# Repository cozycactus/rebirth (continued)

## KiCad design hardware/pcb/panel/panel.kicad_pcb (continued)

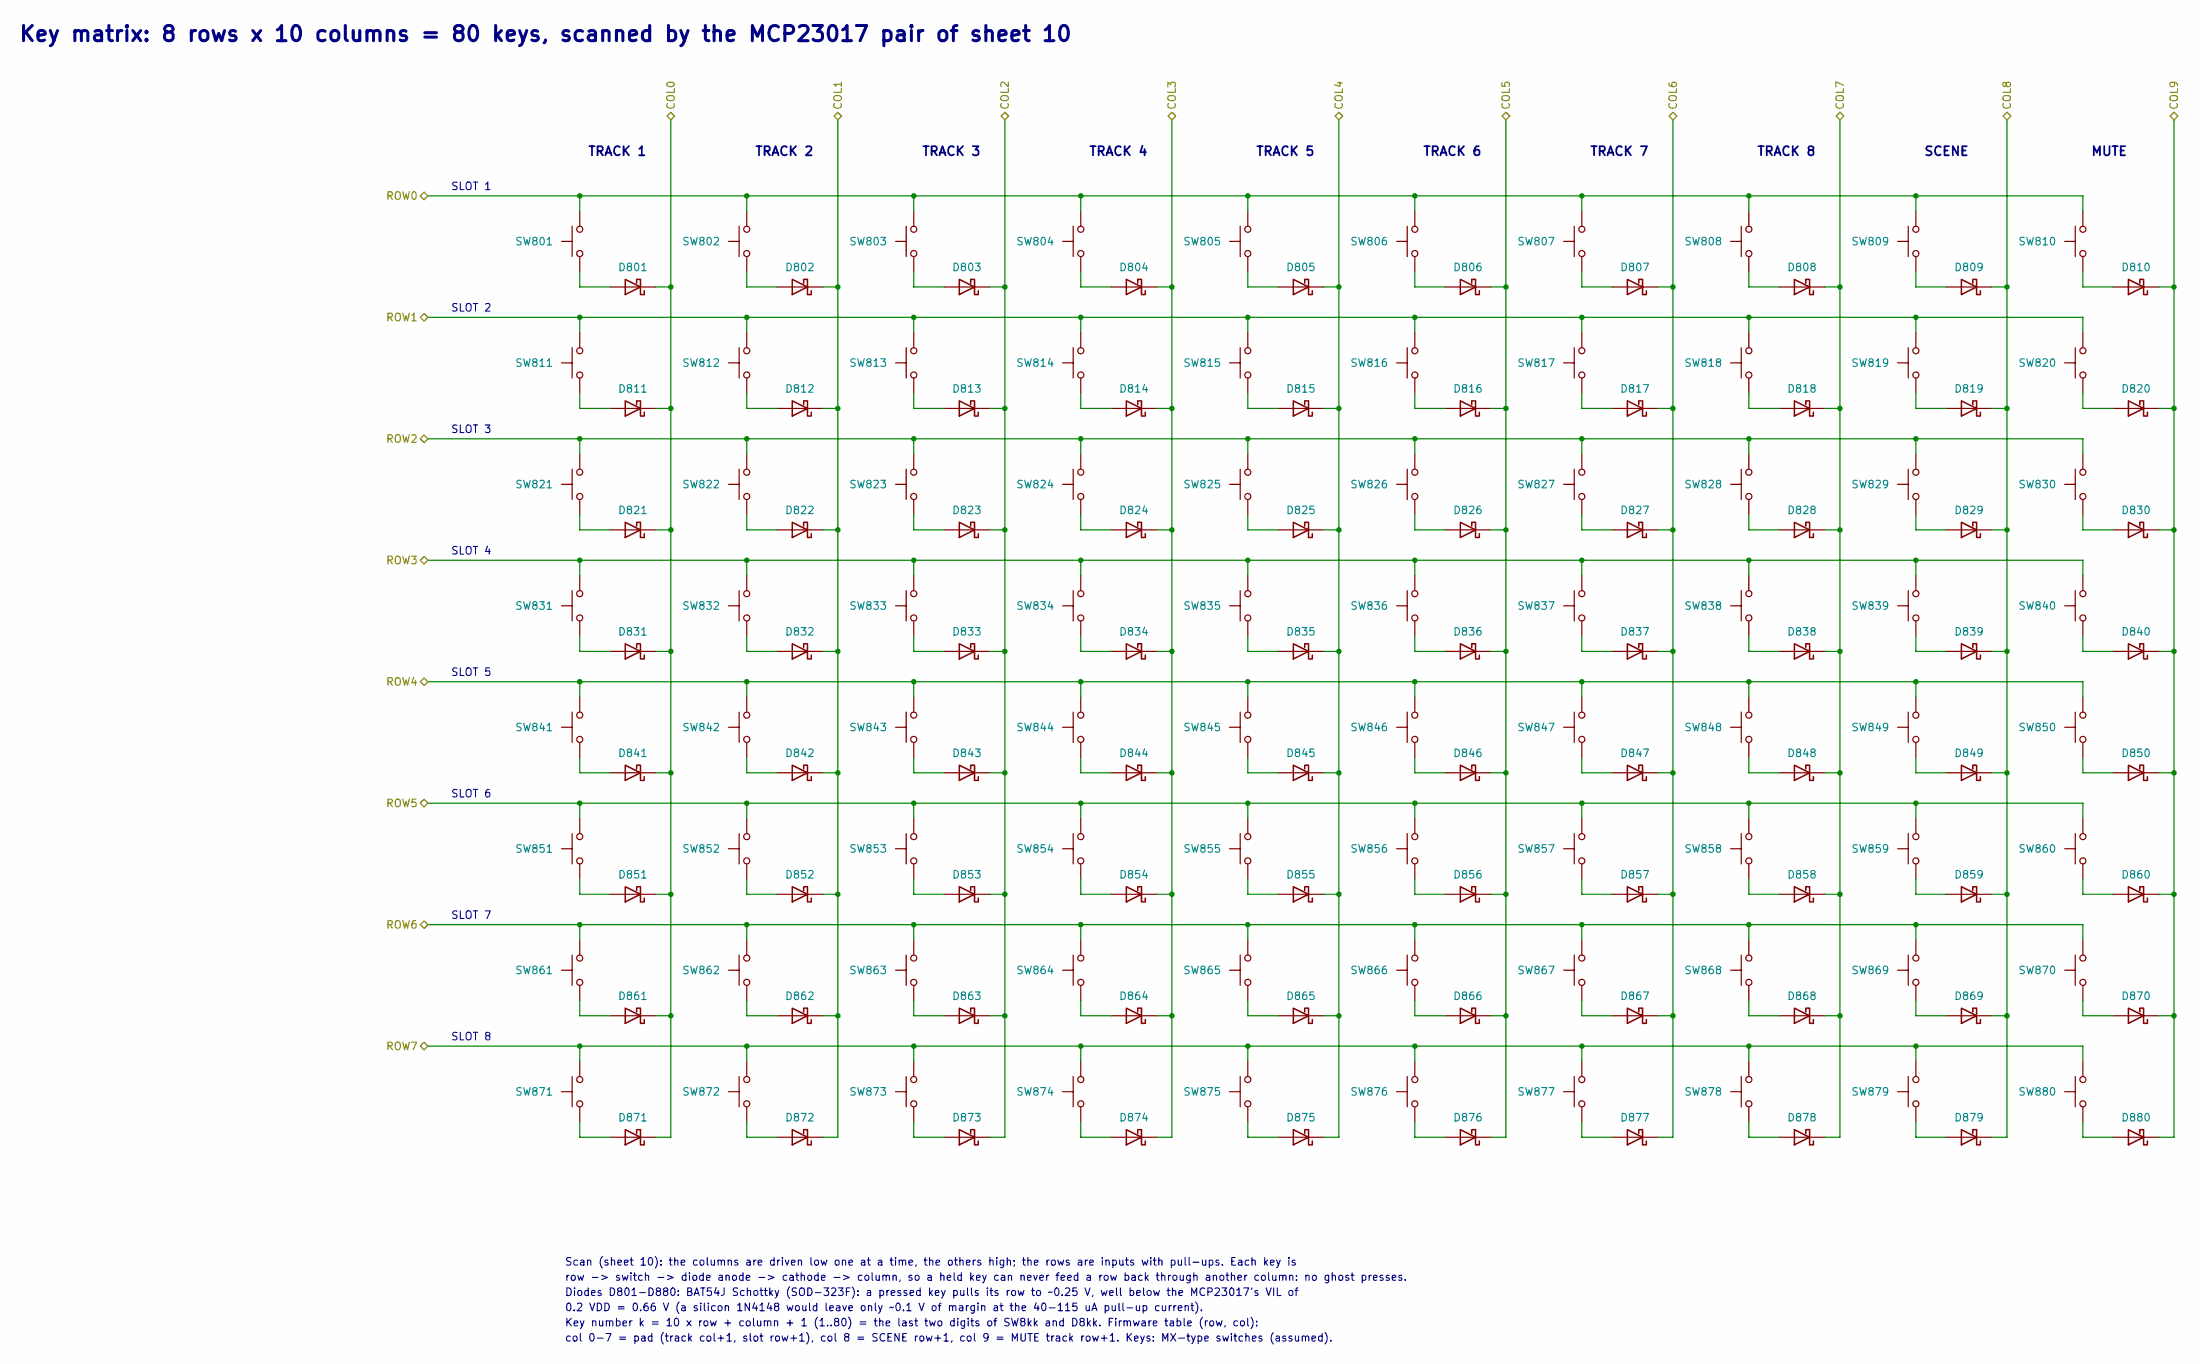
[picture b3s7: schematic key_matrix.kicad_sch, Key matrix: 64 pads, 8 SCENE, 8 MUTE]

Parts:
D801, D802, D803, D804, D805, D806, D807, D808, D809, D810, D811, D812, D813, D814, D815, D816, D817, D818, D819, D820, D821, D822, D823, D824, D825, D826, D827, D828, D829, D830, D831, D832, D833, D834, D835, D836, D837, D838, D839, D840, D841, D842, D843, D844, D845, D846, D847, D848, D849, D850, D851, D852, D853, D854, D855, D856, D857, D858, D859, D860, D861, D862, D863, D864, D865, D866, D867, D868, D869, D870, D871, D872, D873, D874, D875, D876, D877, D878, D879, D880: BAT54J; D_SOD-323F
SW801, SW802, SW803, SW804, SW805, SW806, SW807, SW808, SW809, SW810, SW811, SW812, SW813, SW814, SW815, SW816, SW817, SW818, SW819, SW820, SW821, SW822, SW823, SW824, SW825, SW826, SW827, SW828, SW829, SW830, SW831, SW832, SW833, SW834, SW835, SW836, SW837, SW838, SW839, SW840, SW841, SW842, SW843, SW844, SW845, SW846, SW847, SW848, SW849, SW850, SW851, SW852, SW853, SW854, SW855, SW856, SW857, SW858, SW859, SW860, SW861, SW862, SW863, SW864, SW865, SW866, SW867, SW868, SW869, SW870, SW871, SW872, SW873, SW874, SW875, SW876, SW877, SW878, SW879, SW880: MX; SW_Cherry_MX_1.00u_PCB

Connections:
/COL0: D801.1 (K), D811.1 (K), D821.1 (K), D831.1 (K), D841.1 (K), D851.1 (K), D861.1 (K), D871.1 (K); also elsewhere on the board
/COL1: D802.1 (K), D812.1 (K), D822.1 (K), D832.1 (K), D842.1 (K), D852.1 (K), D862.1 (K), D872.1 (K); also elsewhere on the board
/COL2: D803.1 (K), D813.1 (K), D823.1 (K), D833.1 (K), D843.1 (K), D853.1 (K), D863.1 (K), D873.1 (K); also elsewhere on the board
/COL3: D804.1 (K), D814.1 (K), D824.1 (K), D834.1 (K), D844.1 (K), D854.1 (K), D864.1 (K), D874.1 (K); also elsewhere on the board
/COL4: D805.1 (K), D815.1 (K), D825.1 (K), D835.1 (K), D845.1 (K), D855.1 (K), D865.1 (K), D875.1 (K); also elsewhere on the board
/COL5: D806.1 (K), D816.1 (K), D826.1 (K), D836.1 (K), D846.1 (K), D856.1 (K), D866.1 (K), D876.1 (K); also elsewhere on the board
/COL6: D807.1 (K), D817.1 (K), D827.1 (K), D837.1 (K), D847.1 (K), D857.1 (K), D867.1 (K), D877.1 (K); also elsewhere on the board
/COL7: D808.1 (K), D818.1 (K), D828.1 (K), D838.1 (K), D848.1 (K), D858.1 (K), D868.1 (K), D878.1 (K); also elsewhere on the board
/COL8: D809.1 (K), D819.1 (K), D829.1 (K), D839.1 (K), D849.1 (K), D859.1 (K), D869.1 (K), D879.1 (K); also elsewhere on the board
/COL9: D810.1 (K), D820.1 (K), D830.1 (K), D840.1 (K), D850.1 (K), D860.1 (K), D870.1 (K), D880.1 (K); also elsewhere on the board
/ROW0: SW801.2, SW802.2, SW803.2, SW804.2, SW805.2, SW806.2, SW807.2, SW808.2, SW809.2, SW810.2; also elsewhere on the board
/ROW1: SW811.2, SW812.2, SW813.2, SW814.2, SW815.2, SW816.2, SW817.2, SW818.2, SW819.2, SW820.2; also elsewhere on the board
/ROW2: SW821.2, SW822.2, SW823.2, SW824.2, SW825.2, SW826.2, SW827.2, SW828.2, SW829.2, SW830.2; also elsewhere on the board
/ROW3: SW831.2, SW832.2, SW833.2, SW834.2, SW835.2, SW836.2, SW837.2, SW838.2, SW839.2, SW840.2; also elsewhere on the board
/ROW4: SW841.2, SW842.2, SW843.2, SW844.2, SW845.2, SW846.2, SW847.2, SW848.2, SW849.2, SW850.2; also elsewhere on the board
/ROW5: SW851.2, SW852.2, SW853.2, SW854.2, SW855.2, SW856.2, SW857.2, SW858.2, SW859.2, SW860.2; also elsewhere on the board
/ROW6: SW861.2, SW862.2, SW863.2, SW864.2, SW865.2, SW866.2, SW867.2, SW868.2, SW869.2, SW870.2; also elsewhere on the board
/ROW7: SW871.2, SW872.2, SW873.2, SW874.2, SW875.2, SW876.2, SW877.2, SW878.2, SW879.2, SW880.2; also elsewhere on the board
unnamed: D801.2 (A), SW801.1
unnamed: D802.2 (A), SW802.1
unnamed: D803.2 (A), SW803.1
unnamed: D804.2 (A), SW804.1
unnamed: D805.2 (A), SW805.1
unnamed: D806.2 (A), SW806.1
unnamed: D807.2 (A), SW807.1
unnamed: D808.2 (A), SW808.1
unnamed: D809.2 (A), SW809.1
unnamed: D810.2 (A), SW810.1
unnamed: D811.2 (A), SW811.1
unnamed: D812.2 (A), SW812.1
unnamed: D813.2 (A), SW813.1
unnamed: D814.2 (A), SW814.1
unnamed: D815.2 (A), SW815.1
unnamed: D816.2 (A), SW816.1
unnamed: D817.2 (A), SW817.1
unnamed: D818.2 (A), SW818.1
unnamed: D819.2 (A), SW819.1
unnamed: D820.2 (A), SW820.1
unnamed: D821.2 (A), SW821.1
unnamed: D822.2 (A), SW822.1
unnamed: D823.2 (A), SW823.1
unnamed: D824.2 (A), SW824.1
unnamed: D825.2 (A), SW825.1
unnamed: D826.2 (A), SW826.1
unnamed: D827.2 (A), SW827.1
unnamed: D828.2 (A), SW828.1
unnamed: D829.2 (A), SW829.1
unnamed: D830.2 (A), SW830.1
unnamed: D831.2 (A), SW831.1
unnamed: D832.2 (A), SW832.1
unnamed: D833.2 (A), SW833.1
unnamed: D834.2 (A), SW834.1
unnamed: D835.2 (A), SW835.1
unnamed: D836.2 (A), SW836.1
unnamed: D837.2 (A), SW837.1
unnamed: D838.2 (A), SW838.1
unnamed: D839.2 (A), SW839.1
unnamed: D840.2 (A), SW840.1
unnamed: D841.2 (A), SW841.1
unnamed: D842.2 (A), SW842.1
unnamed: D843.2 (A), SW843.1
unnamed: D844.2 (A), SW844.1
unnamed: D845.2 (A), SW845.1
unnamed: D846.2 (A), SW846.1
unnamed: D847.2 (A), SW847.1
unnamed: D848.2 (A), SW848.1
unnamed: D849.2 (A), SW849.1
unnamed: D850.2 (A), SW850.1
unnamed: D851.2 (A), SW851.1
unnamed: D852.2 (A), SW852.1
unnamed: D853.2 (A), SW853.1
unnamed: D854.2 (A), SW854.1
unnamed: D855.2 (A), SW855.1
unnamed: D856.2 (A), SW856.1
unnamed: D857.2 (A), SW857.1
unnamed: D858.2 (A), SW858.1
unnamed: D859.2 (A), SW859.1
unnamed: D860.2 (A), SW860.1
unnamed: D861.2 (A), SW861.1
unnamed: D862.2 (A), SW862.1
unnamed: D863.2 (A), SW863.1
unnamed: D864.2 (A), SW864.1
unnamed: D865.2 (A), SW865.1
unnamed: D866.2 (A), SW866.1
unnamed: D867.2 (A), SW867.1
unnamed: D868.2 (A), SW868.1
unnamed: D869.2 (A), SW869.1
unnamed: D870.2 (A), SW870.1
unnamed: D871.2 (A), SW871.1
unnamed: D872.2 (A), SW872.1
unnamed: D873.2 (A), SW873.1
unnamed: D874.2 (A), SW874.1
unnamed: D875.2 (A), SW875.1
unnamed: D876.2 (A), SW876.1
unnamed: D877.2 (A), SW877.1
unnamed: D878.2 (A), SW878.1
unnamed: D879.2 (A), SW879.1
unnamed: D880.2 (A), SW880.1

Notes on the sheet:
Key matrix: 8 rows x 10 columns = 80 keys, scanned by the MCP23017 pair of sheet 10
SLOT 1
SLOT 2
SLOT 3
SLOT 4
SLOT 5
SLOT 6
SLOT 7
SLOT 8
TRACK 1
TRACK 2
TRACK 3
TRACK 4
TRACK 5
TRACK 6
TRACK 7
TRACK 8
SCENE
MUTE
Scan (sheet 10): the columns are driven low one at a time, the others high; the rows are inputs with pull-ups. Each key is
row -> switch -> diode anode -> cathode -> column, so a held key can never feed a row back through another column: no ghost presses.
Diodes D801-D880: BAT54J Schottky (SOD-323F): a pressed key pulls its row to ~0.25 V, well below the MCP23017's VIL of
0.2 VDD = 0.66 V (a silicon 1N4148 would leave only ~0.1 V of margin at the 40-115 uA pull-up current).
Key number k = 10 x row + column + 1 (1..80) = the last two digits of SW8kk and D8kk. Firmware table (row, col):
col 0-7 = pad (track col+1, slot row+1), col 8 = SCENE row+1, col 9 = MUTE track row+1. Keys: MX-type switches (assumed).

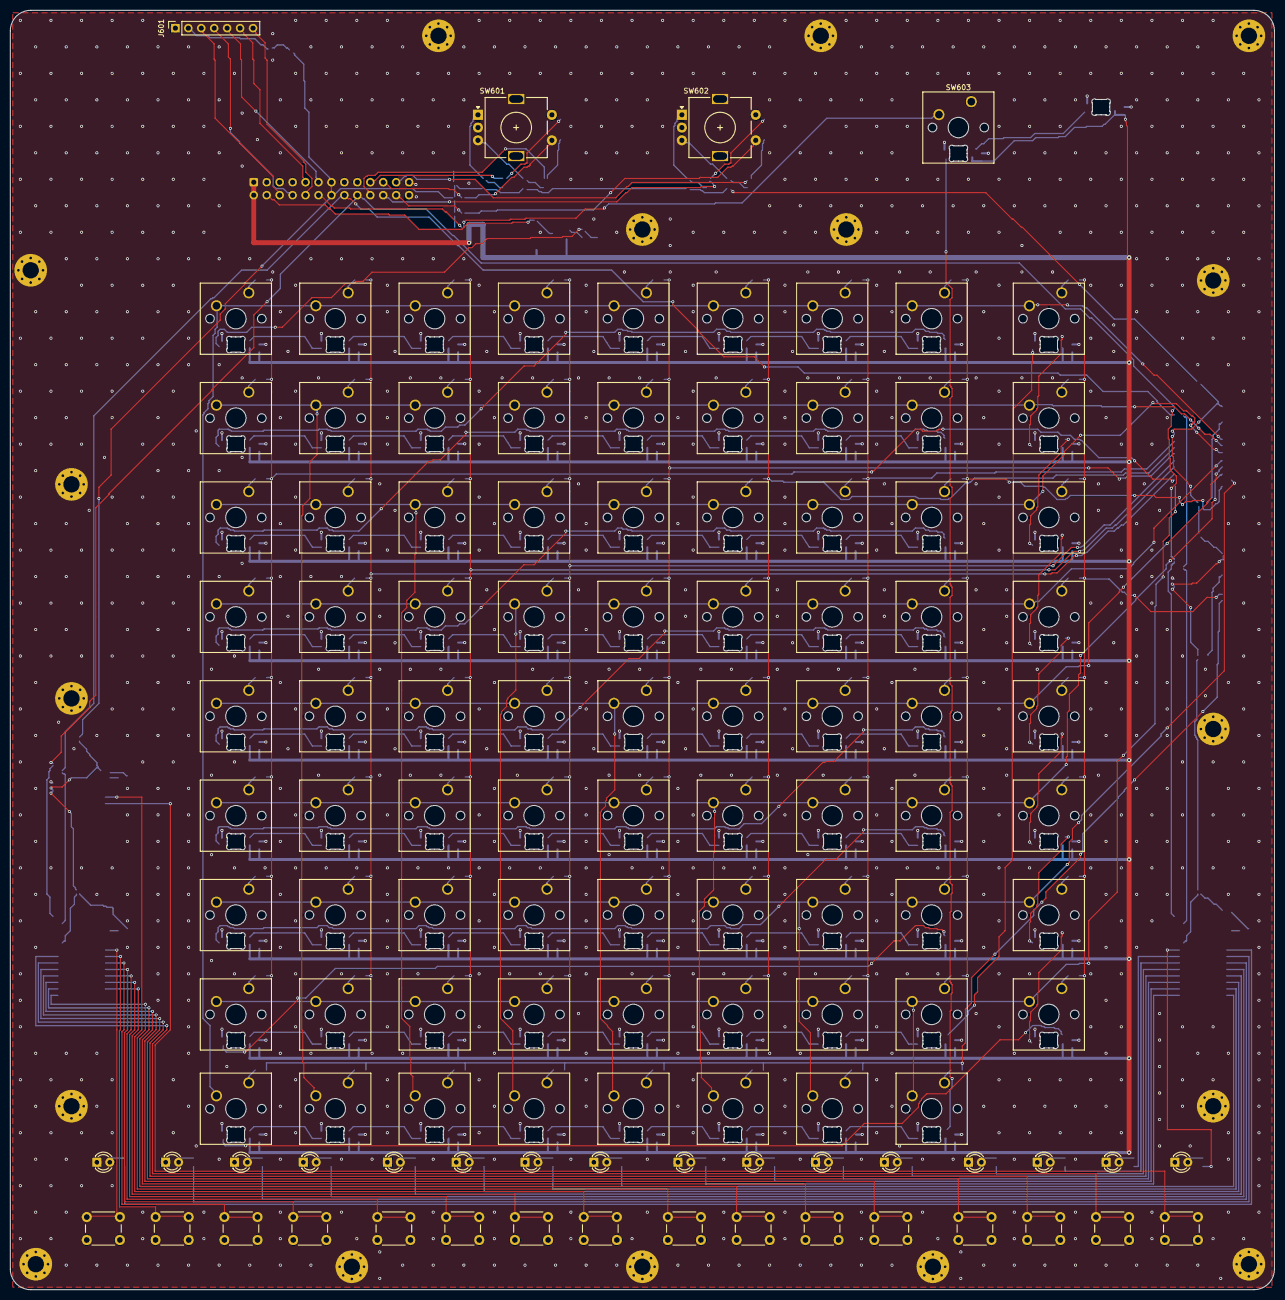
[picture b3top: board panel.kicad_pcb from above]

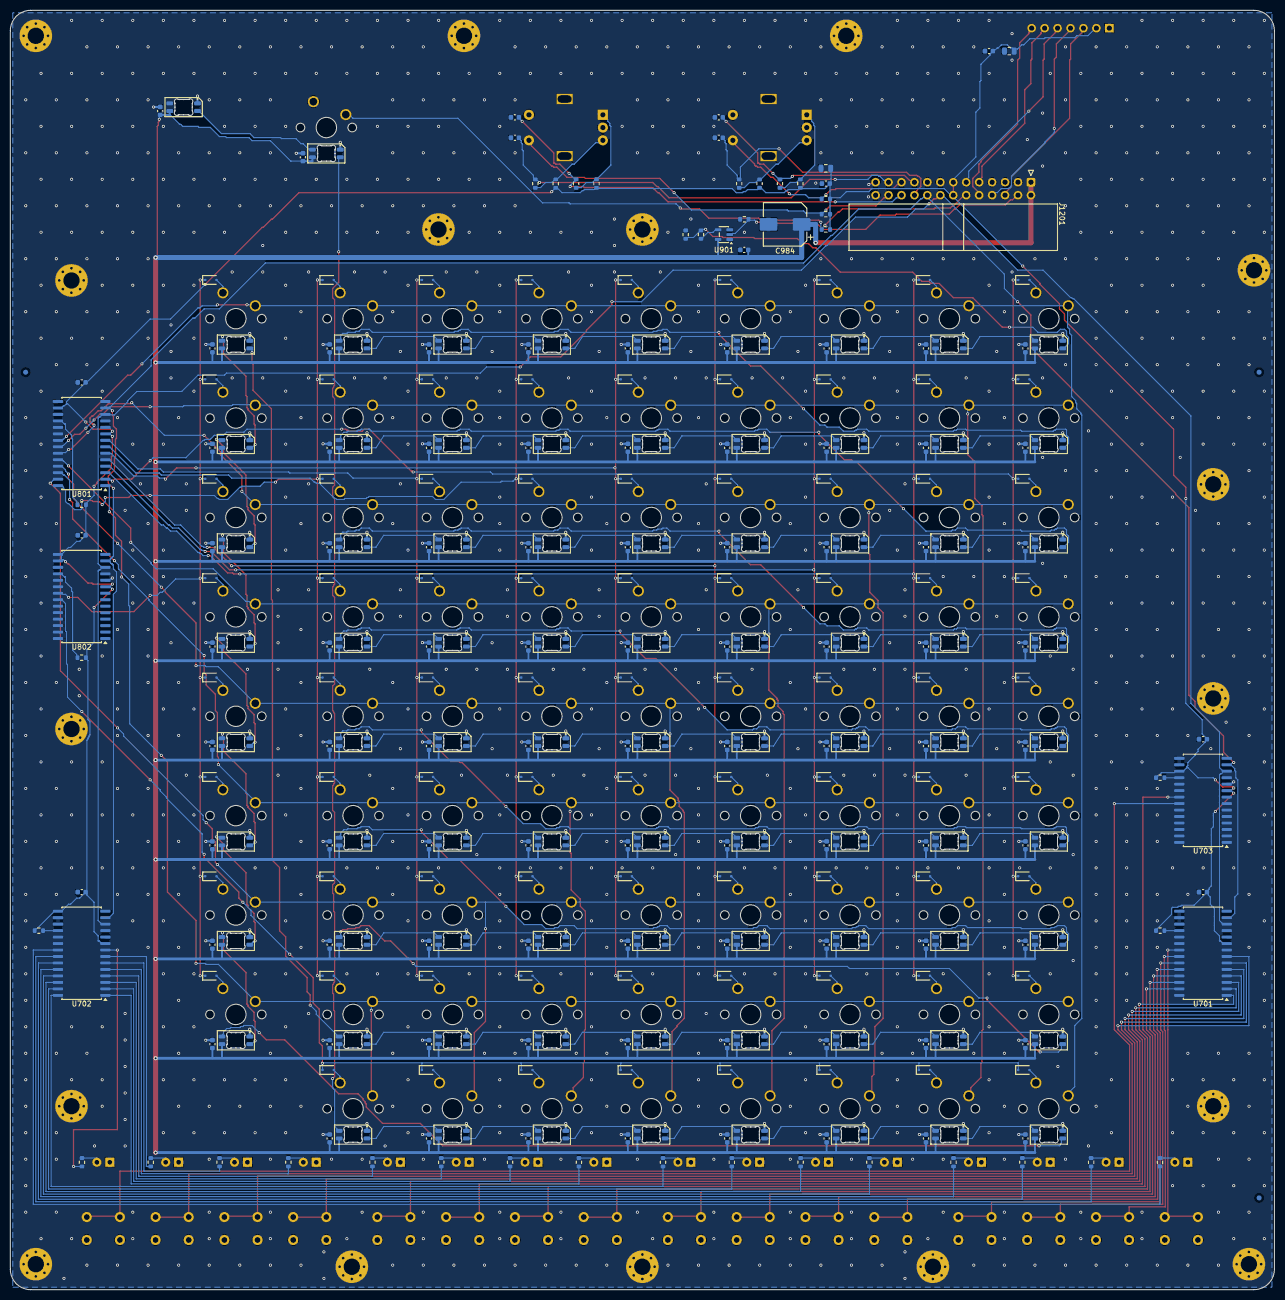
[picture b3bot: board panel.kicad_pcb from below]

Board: 2 copper layers, 248.0 x 251.0 mm, 437 parts (304 on the bottom side), 256 nets.

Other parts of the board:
FID1, FID2, FID3: Fiducial_1mm_Mask2mm
H1, H2, H3, H4, H5, H6, H7, H8, H9, H10, H11, H12, H13, H14, H15, H16, H17: MountingHole_3.2mm_M3_Pad_Via

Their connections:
GND: H1.1, H2.1, H3.1, H4.1, H5.1, H6.1, H7.1, H8.1, H9.1, H10.1, H11.1, H12.1, H13.1, H14.1, H15.1, H16.1, H17.1; also elsewhere on the board

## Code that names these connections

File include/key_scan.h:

#ifndef KEY_SCAN_H
#define KEY_SCAN_H

#include <stdbool.h>
#include <stdint.h>

// The 8 x 10 key matrix on two MCP23017 (I2C0, BANK = 0). Each key is
// row -> switch -> diode -> column: rows are inputs with pull-ups, columns
// push-pull outputs, the selected one low.
#define KEY_SCAN_ROW_ADDR 0x22   // U801: GPA0-6 = ROW0-6, GPB0 = ROW7, GPB1-7 = COL0-6, GPA7 = COL7
#define KEY_SCAN_COL_ADDR 0x23   // U802: GPA0 = COL8, GPA1 = COL9, other pins open
#define KEY_SCAN_ROWS 8
#define KEY_SCAN_COLS 10

// Configures both chips, IODIR (the canary) first on each: U801 IODIR 7F/01,
// IPOL 00/00, GPPU 7F/01, OLAT FF/FF, then U802 IODIR 00/00, OLAT FF/FF.
// Does not bring the bus up (mcp23017_init does). The column selection is
// unknown afterwards, whatever the result.
bool key_scan_init(void);

// Reads U801 IODIR and IPOL and U802 IODIR back. False on an I2C error;
// otherwise *intact tells whether all six bytes hold what key_scan_init
// wrote. A chip that reset after its canary was written reads not intact.
bool key_scan_check(bool *intact);

// Selects column col (0-9) and reads the rows: *down bit r = ROW r low. A
// column that may still be low is released first, so at most one column is
// low when the rows are read. False on an I2C error: *down is not written
// and the selection becomes unknown, so the next step releases both chips'
// columns as needed. A col of KEY_SCAN_COLS or more is refused: false, with
// no transfer and the selection unchanged.
bool key_scan_column(uint8_t col, uint8_t *down);

// Reads back only the canaries a reset clears, after the sample of column col
// (0-9): U801 IODIR for COL0-7 (pointer write and 2 bytes), and U802 IODIR as
// well for COL8/9. False on an I2C error, or with no transfer for a col of
// KEY_SCAN_COLS or more; *intact is then not written. Otherwise *intact tells
// whether those bytes hold what key_scan_init wrote. IPOL is left to
// key_scan_check. The column selection is not touched.
bool key_scan_verify(uint8_t col, bool *intact);

#endif

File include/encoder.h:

#ifndef ENCODER_H
#define ENCODER_H

#include <stdint.h>
#include <stdbool.h>

// ─── Configuration ─────────────────────────────────────────────

#define NUM_ENCODERS    2

// Encoder 1: Navigation / Track select
#define ENC1_A_PIN      18
#define ENC1_B_PIN      19
#define ENC1_SW_PIN     20

// Encoder 2: Value / Transport
#define ENC2_A_PIN      21
#define ENC2_B_PIN      22
#define ENC2_SW_PIN     26

// Timing
#define ENC_DEBOUNCE_MS     20      // Button debounce window
#define ENC_LONG_PRESS_MS   500     // Long press threshold
#define ENC_ACCEL_FAST_MS   60      // a detent less than this after the last one is fast
#define ENC_ACCEL_LO_AFTER  3       // more fast detents in a row than this: x MULT_LO
#define ENC_ACCEL_HI_AFTER  6       // more than this: x MULT_HI
#define ENC_ACCEL_MULT_LO   4
#define ENC_ACCEL_MULT_HI   8

#define ENC_EDGES_PER_DETENT 4      // quadrature edges per detent (EC11 type: 4)

// ─── Types ─────────────────────────────────────────────────────

typedef enum {
    BTN_NONE,               // No event
    BTN_PRESS,              // Short press (fired on release, <500ms)
    BTN_LONG_PRESS,         // Long press (fired while held, >500ms)
    BTN_RELEASE,            // Release after long press
} button_event_t;

// Detent-rate acceleration of one encoder (encoder_accel_detent).
typedef struct {
    uint32_t        last_ms;            // time of the last detent
    int8_t          last_dir;           // its direction (+1, -1; 0 before the first)
    uint8_t         fast;               // fast detents in a row, saturating
} encoder_accel_t;

// One encoder's turn since the last read. A choice (a list row, a type, a
// slot, a lane, a stop) moves by `detents`, one per click however fast; a
// number moves by `amount`, the same clicks accelerated on a fast turn.
typedef struct {
    int8_t          detents;            // whole detents, + clockwise
    int8_t          amount;             // the detents, each x1, x4 or x8
} encoder_turn_t;

typedef struct {
    // Public — consumed by caller
    button_event_t  button_event;       // Current button event
    bool            button_held;        // True while button is physically held

    // Internal — do not access directly
    uint8_t         _prev_ab;           // Previous A/B pin state (2 bits)
    uint32_t        _btn_down_ms;       // Timestamp of button press
    bool            _btn_raw;           // Current debounced button state
    bool            _btn_prev;          // Previous debounced state
    uint32_t        _btn_debounce_ms;   // Last debounce sample time
    bool            _long_fired;        // Long press already emitted
    int8_t          _edges;             // edges of the detent in progress
    int16_t         _detents;           // whole detents not yet read
    int16_t         _amount;            // their accelerated amount
    encoder_accel_t _accel;
} encoder_state_t;

// ─── API ───────────────────────────────────────────────────────

// Initialize GPIO pins (pull-ups, input mode)
void encoder_init(void);

// Poll all encoders — call as often as possible from ui_update()
void encoder_poll(void);

// After a flash stall: each button's state now becomes its debounced state.
// A button released during the stall reports nothing; one held through it
// never becomes BTN_PRESS or BTN_LONG_PRESS (its release is BTN_RELEASE).
void encoder_resync(void);

// Read and consume the turn since the last call: whole detents
// (ENC_EDGES_PER_DETENT edges each; a detent in progress stays for the next
// call) and their accelerated amount. Positive = clockwise.
encoder_turn_t encoder_get_turn(uint8_t enc);

// Read and consume button event
button_event_t encoder_get_button(uint8_t enc);

// Check if button is currently held (non-consuming)
bool encoder_button_held(uint8_t enc);

// ─── Acceleration ──────────────────────────────────────────────

// Counts one detent in direction `dir` (+1 or -1) at `now_ms` and returns what
// it is worth to a number. A detent less than ENC_ACCEL_FAST_MS after the last
// one, in the same direction, is fast. After more than ENC_ACCEL_LO_AFTER fast
// detents in a row each is worth ENC_ACCEL_MULT_LO, and after more than
// ENC_ACCEL_HI_AFTER, ENC_ACCEL_MULT_HI. A slow detent or a turn back is worth 1
// and starts over. The one place numbers are accelerated; the UI test's encoder
// fake shares it.
static inline int8_t encoder_accel_detent(encoder_accel_t *a, int8_t dir, uint32_t now_ms) {
    if (dir == a->last_dir && now_ms - a->last_ms < ENC_ACCEL_FAST_MS) {
        if (a->fast < UINT8_MAX) a->fast++;
    } else {
        a->fast = 0;
    }
    a->last_ms = now_ms;
    a->last_dir = dir;
    if (a->fast > ENC_ACCEL_HI_AFTER) return ENC_ACCEL_MULT_HI;
    if (a->fast > ENC_ACCEL_LO_AFTER) return ENC_ACCEL_MULT_LO;
    return 1;
}

#endif // ENCODER_H

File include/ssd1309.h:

#ifndef SSD1309_H
#define SSD1309_H

#include <stdint.h>
#include <stdbool.h>

// ─── SPI0 Pin Assignments ──────────────────────────────────────
#define OLED_SCK_PIN    2
#define OLED_MOSI_PIN   3
#define OLED_CS_PIN     4
#define OLED_DC_PIN     5
#define OLED_RST_PIN    6

// ─── Display Dimensions ────────────────────────────────────────
#define OLED_WIDTH      128
#define OLED_HEIGHT     64
#define OLED_PAGES      (OLED_HEIGHT / 8)               // 8 pages
#define OLED_BUF_SIZE   (OLED_WIDTH * OLED_PAGES)       // 1024 bytes

// ─── Font Metrics ──────────────────────────────────────────────
#define FONT_CHAR_W     6       // 5px glyph + 1px spacing
#define FONT_CHAR_H     8       // 7px glyph + 1px spacing
#define FONT_COLS       (OLED_WIDTH / FONT_CHAR_W)      // 21 chars per line
#define FONT_ROWS       (OLED_HEIGHT / FONT_CHAR_H)     // 8 text lines

// ─── Lifecycle ─────────────────────────────────────────────────

// Initialize SPI0, reset display, send SSD1309 init sequence
void ssd1309_init(void);

// ─── Framebuffer Operations ────────────────────────────────────

// Clear framebuffer (all pixels off)
void ssd1309_clear(void);

// Push entire framebuffer to display via SPI
void ssd1309_flush(void);

// Direct access to the 1024-byte framebuffer
uint8_t *ssd1309_get_framebuffer(void);

// ─── Pixel Operations ──────────────────────────────────────────

void ssd1309_set_pixel(uint8_t x, uint8_t y, bool on);
bool ssd1309_get_pixel(uint8_t x, uint8_t y);

// ─── Drawing Primitives ────────────────────────────────────────

void ssd1309_draw_hline(uint8_t x0, uint8_t x1, uint8_t y, bool on);
void ssd1309_draw_vline(uint8_t x, uint8_t y0, uint8_t y1, bool on);
void ssd1309_draw_rect(uint8_t x, uint8_t y, uint8_t w, uint8_t h, bool on);
void ssd1309_fill_rect(uint8_t x, uint8_t y, uint8_t w, uint8_t h, bool on);

// ─── Text ──────────────────────────────────────────────────────

// Draw single character at pixel position. invert=true for highlight.
void ssd1309_draw_char(uint8_t x, uint8_t y, char c, bool invert);

// Draw null-terminated string. Wraps are NOT handled — caller clips.
void ssd1309_draw_string(uint8_t x, uint8_t y, const char *str, bool invert);

// ─── Display Control ───────────────────────────────────────────

void ssd1309_set_contrast(uint8_t val);

#endif // SSD1309_H

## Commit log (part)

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2026-03-05 Initial commit: RP2040 sequencer with song mode
    - Project structure: src/, include/, test/
    - 8-track MIDI/CV sequencer engine (96 PPQN, Core 1 ISR)
    - Two-phase commit for simultaneous track sync
    - Song mode with pattern chaining and A/B variations
    - Pattern queue (switch patterns during playback)
    - Track mutes (bitmask-based)
2026-03-05 Add README
2026-03-09 Add VS Code presets/tasks and multiplatform CI workflow
2026-03-09 Initial plan
2026-03-09 Fix CI: initialize Pico SDK submodules to provide tusb.h
2026-03-09 Remove USB MIDI (TinyUSB) — dawless setup needs only DIN-5 MIDI
    Drop tusb.h include, tud_init/tud_task calls, USB TX ring buffer,
    midi_usb_task(), and usb_descriptors.c from the build. Fixes CI build
    failure caused by uninitialized TinyUSB submodule.
    https://claude.ai/code/session_01M9seHH3GJp3Ev74XSBSrxT
2026-03-09 Add variable pattern length with runtime UI control
2026-03-09 Add step-button LED activity visualization
2026-03-16 Update VS Code and CMake config for Pico SDK VS Code extension
    - Replace shell-based tasks with process-based Pico SDK tasks
    (Compile, Run, Flash, Rescue Reset, RISC-V Reset)
    - Add pico-vscode integration to CMakeLists.txt
    - Use local pico_sdk_import.cmake instead of env-var reference
    - Add PICO_SDK_PATH to CMakePresets.json environments
    - Add VS Code settings for cmake, terminal paths, and pico extension
2026-03-16 fix: update firmware-build CI job to use Pico SDK 2.2.0 at correct path
2026-03-16 fix: create parent directories before cloning Pico SDK
2026-05-24 Improve sequencer jitter and CI
2026-05-25 Add ReBirth-style performance layer
